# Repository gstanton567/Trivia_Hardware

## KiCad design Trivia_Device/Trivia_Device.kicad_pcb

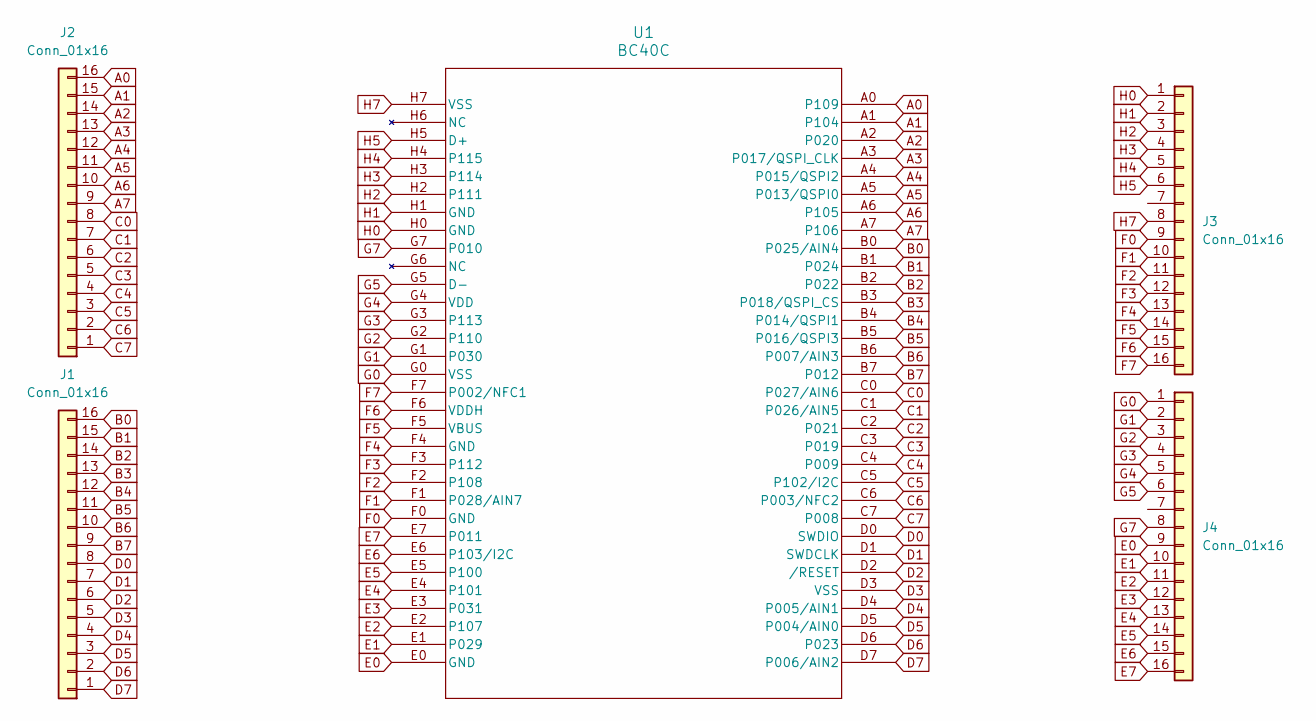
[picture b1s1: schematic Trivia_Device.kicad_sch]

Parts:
J1, J2, J3, J4: Conn_01x16; 1x16 Connector
U1: BC40C; BGA64_BC40C_FNL

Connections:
A0: J2.16, U1.A0 (P109)
A1: J2.15, U1.A1 (P104)
A2: J2.14, U1.A2 (P020)
A3: J2.13, U1.A3 (P017/QSPI_CLK)
A4: J2.12, U1.A4 (P015/QSPI2)
A5: J2.11, U1.A5 (P013/QSPI0)
A6: J2.10, U1.A6 (P105)
A7: J2.9, U1.A7 (P106)
B0: J1.16, U1.B0 (P025/AIN4)
B1: J1.15, U1.B1 (P024)
B2: J1.14, U1.B2 (P022)
B3: J1.13, U1.B3 (P018/QSPI_CS)
B4: J1.12, U1.B4 (P014/QSPI1)
B5: J1.11, U1.B5 (P016/QSPI3)
B6: J1.10, U1.B6 (P007/AIN3)
B7: J1.9, U1.B7 (P012)
C0: J2.8, U1.C0 (P027/AIN6)
C1: J2.7, U1.C1 (P026/AIN5)
C2: J2.6, U1.C2 (P021)
C3: J2.5, U1.C3 (P019)
C4: J2.4, U1.C4 (P009)
C5: J2.3, U1.C5 (P102/I2C)
C6: J2.2, U1.C6 (P003/NFC2)
C7: J2.1, U1.C7 (P008)
D0: J1.8, U1.D0 (SWDIO)
D1: J1.7, U1.D1 (SWDCLK)
D2: J1.6, U1.D2 (/RESET)
D3: J1.5, U1.D3 (VSS)
D4: J1.4, U1.D4 (P005/AIN1)
D5: J1.3, U1.D5 (P004/AIN0)
D6: J1.2, U1.D6 (P023)
D7: J1.1, U1.D7 (P006/AIN2)
E0: J4.9, U1.E0 (GND)
E1: J4.10, U1.E1 (P029)
E2: J4.11, U1.E2 (P107)
E3: J4.12, U1.E3 (P031)
E4: J4.13, U1.E4 (P101)
E5: J4.14, U1.E5 (P100)
E6: J4.15, U1.E6 (P103/I2C)
E7: J4.16, U1.E7 (P011)
F0: J3.9, U1.F0 (GND)
F1: J3.10, U1.F1 (P028/AIN7)
F2: J3.11, U1.F2 (P108)
F3: J3.12, U1.F3 (P112)
F4: J3.13, U1.F4 (GND)
F5: J3.14, U1.F5 (VBUS)
F6: J3.15, U1.F6 (VDDH)
F7: J3.16, U1.F7 (P002/NFC1)
G0: J4.1, U1.G0 (VSS)
G1: J4.2, U1.G1 (P030)
G2: J4.3, U1.G2 (P110)
G3: J4.4, U1.G3 (P113)
G4: J4.5, U1.G4 (VDD)
G5: J4.6, U1.G5 (D-)
G7: J4.8, U1.G7 (P010)
H0: J3.1, U1.H0 (GND)
H1: J3.2, U1.H1 (GND)
H2: J3.3, U1.H2 (P111)
H3: J3.4, U1.H3 (P114)
H4: J3.5, U1.H4 (P115)
H5: J3.6, U1.H5 (D+)
H7: J3.8, U1.H7 (VSS)

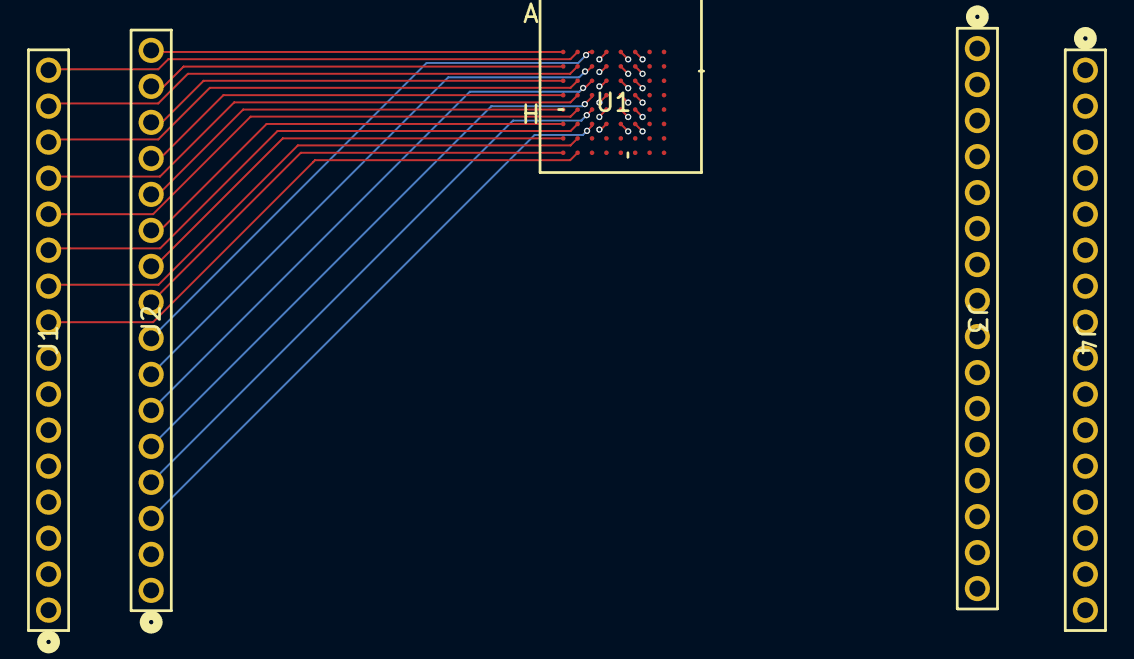
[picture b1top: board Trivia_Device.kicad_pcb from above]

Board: 4 copper layers, 5 parts (0 on the bottom side), 62 nets.

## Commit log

2024-08-29 added blank schematic
2024-09-04 trying to upload new version of schematic
2024-09-14 added whole trivia device folder
2024-09-14 Add rules file in accordance with JLCPCB
    Add a file to define rules/constraints to keep within the
    manufacturing capabilities of JLCPCB. This can be added to KiCAD
    to verify a PCB layout.
    https://jlcpcb.com/capabilities/pcb-capabilities
2024-11-24 working on PCB for processor board
